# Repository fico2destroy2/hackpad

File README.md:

# Hack Pad

Its a keyboard with 4x4 set of keys two rotary encoders and a 128x32 oled display.

## PCB

this project is a stardance mission i tried using only the parts provided from stardamce so my schematic looks like this:

notice that the switches are charlieplexed thats because the provided microcontroller has only 14 pins 11 if you exclude the ground and the power sources the display needs 2 pins
the rotary encoders need 4  that leaves me with 5 I/Os so I charlieplexed them for a total of N × (N - 1) posible swiches witch is 20 in total we got space for 16 switches and for the 2 buttons on the rotary encoder

## CAD

The cad file is split into two parts top and bottom the botom is built to hold the pcb 

the top covers the pcb and holds the display which i will connect to the pcb with wires.

the knobs are for the rotary encoders they have my logo on them thats two Ms in 180 degrees of rotation between them and they are a bit taller because i like them tall

### Bill of Materials (BOM):

1. 1 unsoldered Seeed XIAO RP2040

2. 20x through-hole 1N4148 Diodes

3. 16x MX-Style switches

4. 2x EC11E Rotary encoders (with switch!)

5. 1x 0.91 inch OLED display (the pin order is GND-VCC-SCL-SDA)

6. 16x white blank DSA keycaps

7. 16x SK6812 MINI-E LEDs

8. 6x M3x16mm screws

9. 6x M3x5mx4mm heatset inserts

10. 1x PCB (fabricated using provided files)

### 3D Prints:

 1. 1x Case Top
 
 2. 1x Case Bottom
 
 3. 2x Knob Dials

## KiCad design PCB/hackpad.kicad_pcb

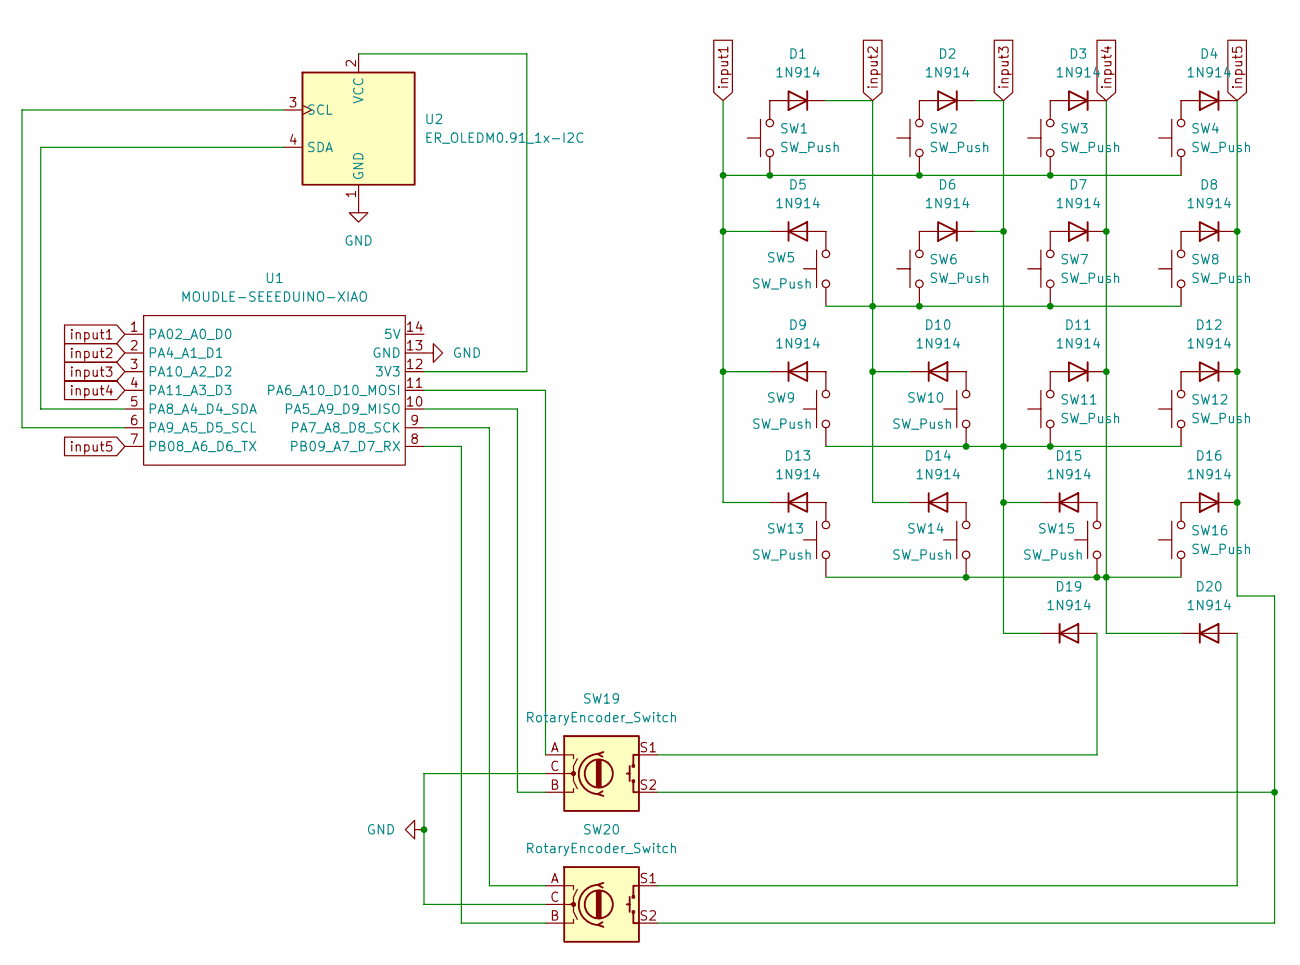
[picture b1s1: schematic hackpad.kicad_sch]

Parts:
D1, D2, D3, D4, D5, D6, D7, D8, D9, D10, D11, D12, D13, D14, D15, D16, D19, D20: 1N914; D_DO-35_SOD27_P7.62mm_Horizontal
SW1, SW2, SW3, SW4, SW5, SW6, SW7, SW8, SW9, SW10, SW11, SW12, SW13, SW14, SW15, SW16: SW_Push; SW_Cherry_MX_1.00u_PCB
SW19, SW20: RotaryEncoder_Switch; RotaryEncoder_Alps_EC11E-Switch_Vertical_H20mm
U1: MOUDLE-SEEEDUINO-XIAO; XIAO-Generic-Hybrid-14P-2.54-21X17.8MM
U2: ER_OLEDM0.91_1x-I2C

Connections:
GND: SW19.C, SW20.C, U1.13 (GND), U2.1 (GND)
unnamed: D1.2 (A), SW1.2
unnamed: D2.2 (A), SW2.2
unnamed: D3.2 (A), SW3.2
unnamed: D4.2 (A), SW4.2
unnamed: D5.2 (A), SW5.2
unnamed: D6.2 (A), SW6.2
unnamed: D7.2 (A), SW7.2
unnamed: D8.2 (A), SW8.2
unnamed: D9.2 (A), SW9.2
unnamed: D10.2 (A), SW10.2
unnamed: D11.2 (A), SW11.2
unnamed: D12.2 (A), SW12.2
unnamed: D13.2 (A), SW13.2
unnamed: D14.2 (A), SW14.2
unnamed: D15.2 (A), SW15.2
unnamed: D16.2 (A), SW16.2
unnamed: D19.2 (A), SW19.S1
unnamed: D20.2 (A), SW20.S1
unnamed: U1.12 (3V3), U2.2 (VCC)
unnamed: SW19.B, U1.10 (PA5_A9_D9_MISO)
unnamed: SW19.A, U1.11 (PA6_A10_D10_MOSI)
unnamed: SW20.A, U1.9 (PA7_A8_D8_SCK)
unnamed: U1.5 (PA8_A4_D4_SDA), U2.4 (SDA)
unnamed: U1.6 (PA9_A5_D5_SCL), U2.3 (SCL)
unnamed: SW20.B, U1.8 (PB09_A7_D7_RX)
input1: D5.1 (K), D9.1 (K), D13.1 (K), SW1.1, SW2.1, SW3.1, SW4.1, U1.1 (PA02_A0_D0)
input2: D1.1 (K), D10.1 (K), D14.1 (K), SW5.1, SW6.1, SW7.1, SW8.1, U1.2 (PA4_A1_D1)
input3: D2.1 (K), D6.1 (K), D15.1 (K), D19.1 (K), SW9.1, SW10.1, SW11.1, SW12.1, U1.3 (PA10_A2_D2)
input4: D3.1 (K), D7.1 (K), D11.1 (K), D20.1 (K), SW13.1, SW14.1, SW15.1, SW16.1, U1.4 (PA11_A3_D3)
input5: D4.1 (K), D8.1 (K), D12.1 (K), D16.1 (K), SW19.S2, SW20.S2, U1.7 (PB08_A6_D6_TX)

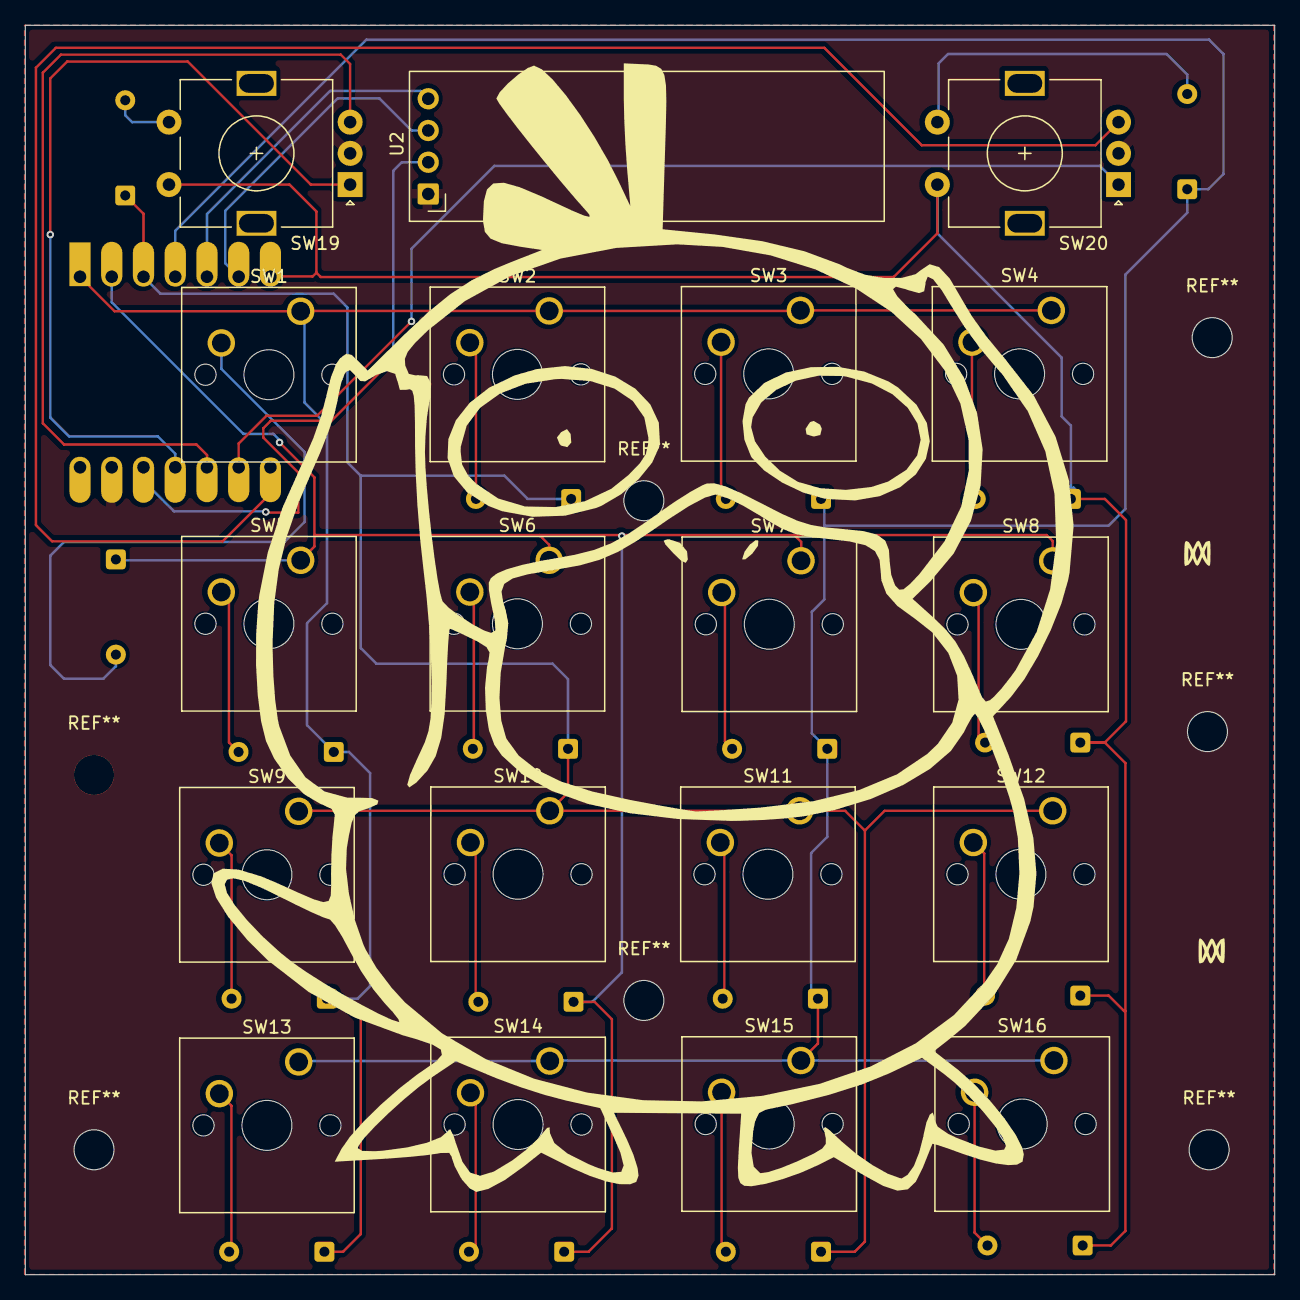
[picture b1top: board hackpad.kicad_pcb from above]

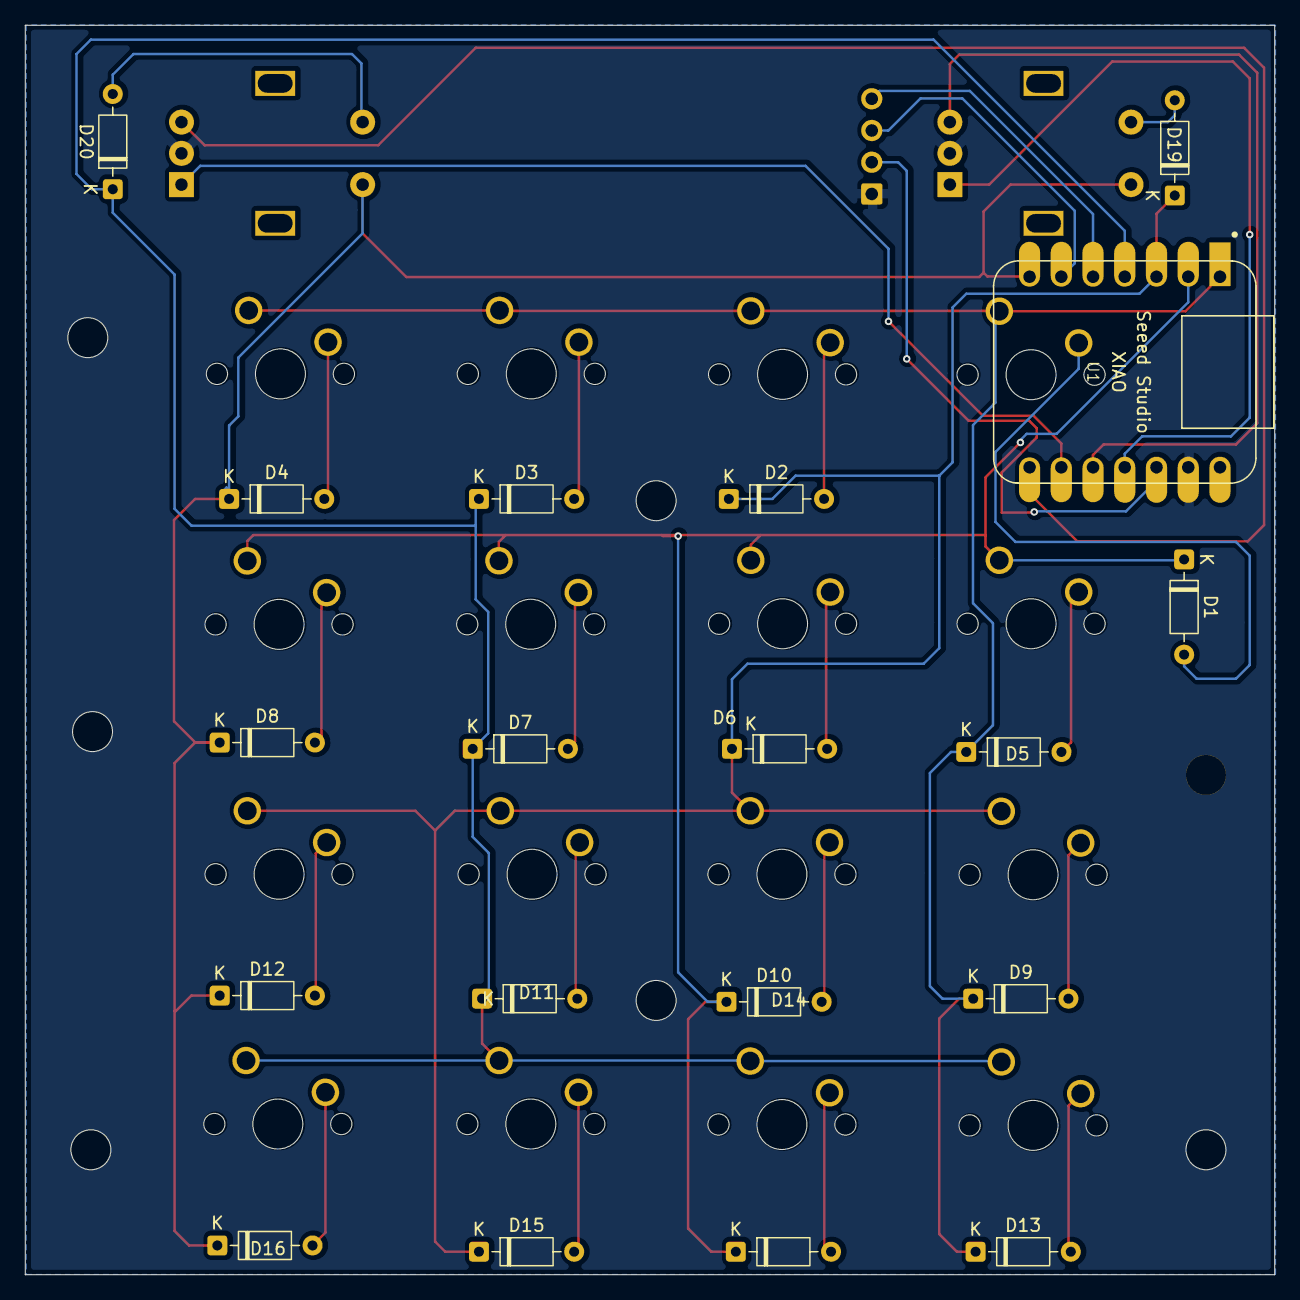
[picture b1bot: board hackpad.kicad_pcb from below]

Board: 2 copper layers, 100.0 x 100.0 mm, 38 parts (19 on the bottom side), 31 nets.
